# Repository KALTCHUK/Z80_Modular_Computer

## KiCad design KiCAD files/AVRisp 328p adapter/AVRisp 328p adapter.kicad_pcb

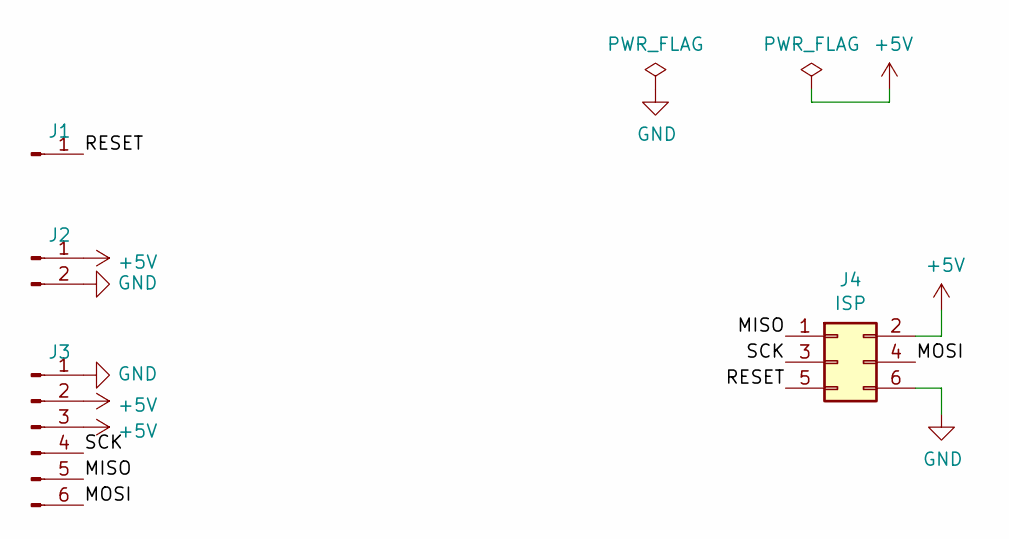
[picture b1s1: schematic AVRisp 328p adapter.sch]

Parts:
J1: Conn_01x01_Male; PinHeader_1x01_P2.54mm_Vertical
J2: Conn_01x02_Male; PinHeader_1x02_P2.54mm_Vertical
J3: Conn_01x06_Male; PinHeader_1x06_P2.54mm_Vertical
J4: ISP; PinHeader_2x03_P2.54mm_Vertical

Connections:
+5V: J2.1, J3.2, J3.3, J4.2
/MISO: J3.5, J4.1
/MOSI: J3.6, J4.4
/RESET: J1.1, J4.5
/SCK: J3.4, J4.3
GND: J2.2, J3.1, J4.6

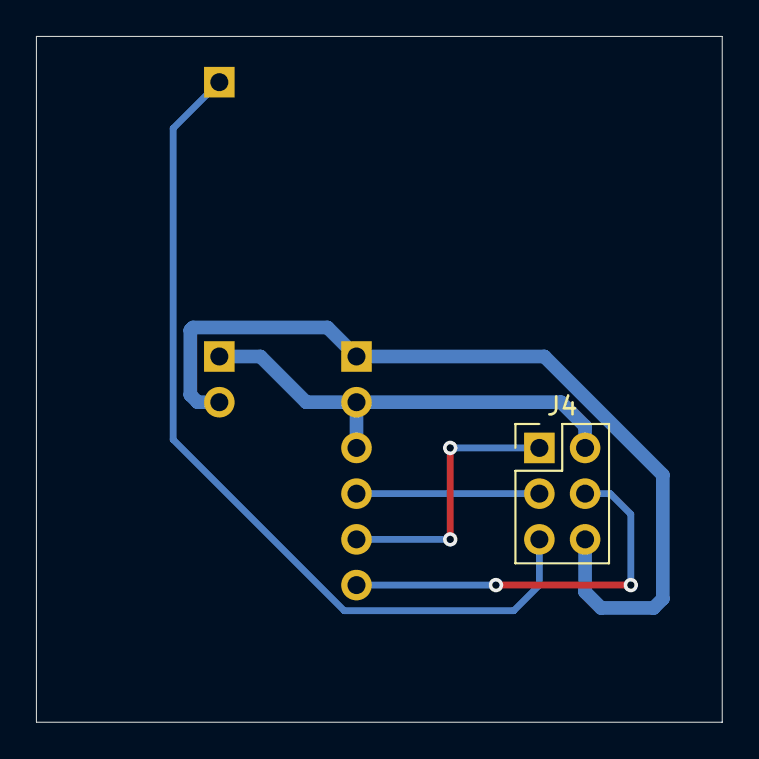
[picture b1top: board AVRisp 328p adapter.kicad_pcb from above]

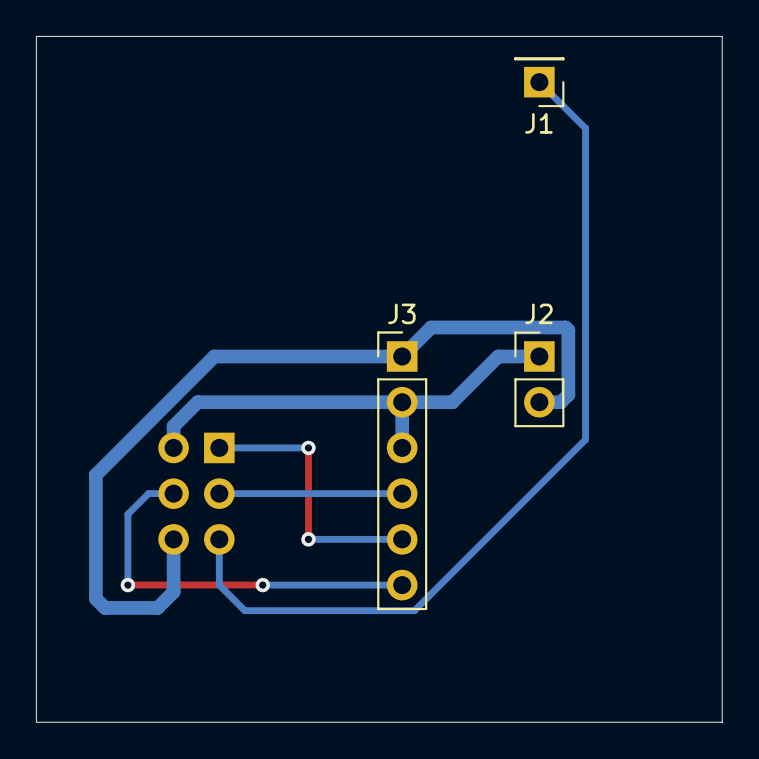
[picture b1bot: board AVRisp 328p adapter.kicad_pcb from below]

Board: 2 copper layers, 38.1 x 38.1 mm, 4 parts (3 on the bottom side), 6 nets.

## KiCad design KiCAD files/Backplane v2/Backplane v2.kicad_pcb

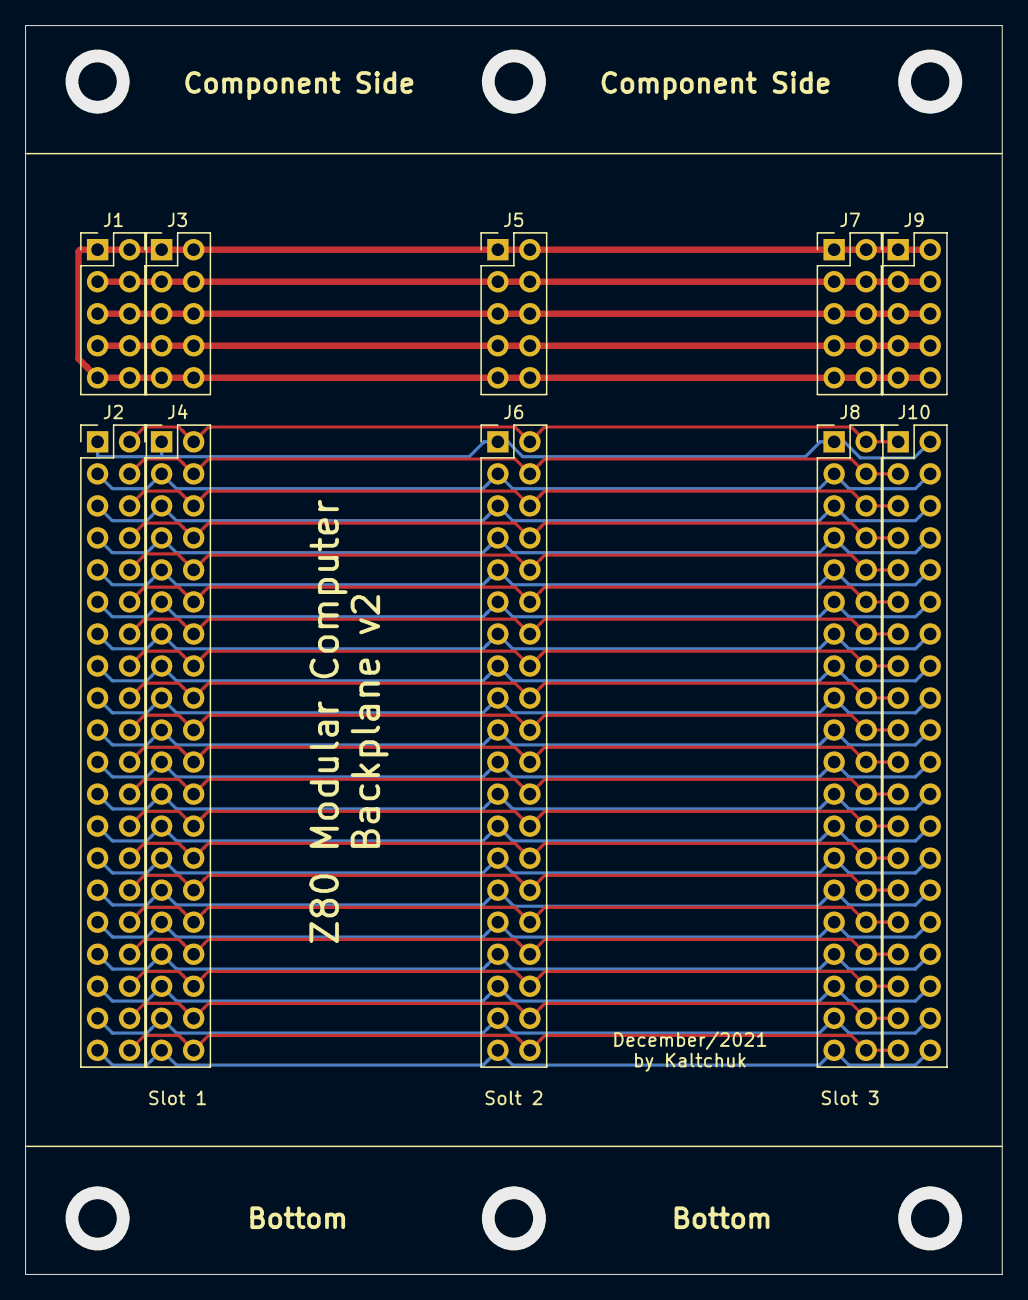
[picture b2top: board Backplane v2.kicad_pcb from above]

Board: 2 copper layers, 77.5 x 99.1 mm, 10 parts (0 on the bottom side), 44 nets.

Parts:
J1, J3, J5, J7, J9: Conn_02x05_Odd_Even; PinHeader_2x05_P2.54mm_Vertical
J2, J4, J6, J8, J10: Conn_02x20_Odd_Even; PinHeader_2x20_P2.54mm_Vertical

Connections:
/+5V: J1.3, J1.4, J3.3, J3.4, J5.3, J5.4, J7.3, J7.4, J9.3, J9.4
/+12V: J1.5, J1.6, J3.5, J3.6, J5.5, J5.6, J7.5, J7.6, J9.5, J9.6
/a00: J2.1, J4.1, J6.1, J8.1, J10.2
/a01: J2.2, J4.2, J6.2, J8.2, J10.1
/a02: J2.3, J4.3, J6.3, J8.3, J10.4
/a03: J2.4, J4.4, J6.4, J8.4, J10.3
/a04: J2.5, J4.5, J6.5, J8.5, J10.6
/a05: J2.6, J4.6, J6.6, J8.6, J10.5
/a06: J2.7, J4.7, J6.7, J8.7, J10.8
/a07: J2.8, J4.8, J6.8, J8.8, J10.7
/a08: J2.9, J4.9, J6.9, J8.9, J10.10
/a09: J2.10, J4.10, J6.10, J8.10, J10.9
/a10: J2.11, J4.11, J6.11, J8.11, J10.12
/a11: J2.12, J4.12, J6.12, J8.12, J10.11
/a12: J2.13, J4.13, J6.13, J8.13, J10.14
/a13: J2.14, J4.14, J6.14, J8.14, J10.13
/a14: J2.15, J4.15, J6.15, J8.15, J10.16
/a15: J2.16, J4.16, J6.16, J8.16, J10.15
/busack: J2.30, J4.30, J6.30, J8.30, J10.29
/busrq: J2.29, J4.29, J6.29, J8.29, J10.30
/clk: J2.40, J4.40, J6.40, J8.40, J10.39
/d00: J2.17, J4.17, J6.17, J8.17, J10.18
/d01: J2.18, J4.18, J6.18, J8.18, J10.17
/d02: J2.19, J4.19, J6.19, J8.19, J10.20
/d03: J2.20, J4.20, J6.20, J8.20, J10.19
/d04: J2.21, J4.21, J6.21, J8.21, J10.22
/d05: J2.22, J4.22, J6.22, J8.22, J10.21
/d06: J2.23, J4.23, J6.23, J8.23, J10.24
/d07: J2.24, J4.24, J6.24, J8.24, J10.23
/gnd: J1.1, J1.2, J1.9, J1.10, J3.1, J3.2, J3.9, J3.10, J5.1, J5.2, J5.9, J5.10, J7.1, J7.2, J7.9, J7.10, J9.1, J9.2, J9.9, J9.10
/halt: J2.32, J4.32, J6.32, J8.32, J10.31
/int: J2.34, J4.34, J6.34, J8.34, J10.33
/iorq: J2.27, J4.27, J6.27, J8.27, J10.28
/m1: J2.38, J4.38, J6.38, J8.38, J10.37
/mreq: J2.25, J4.25, J6.25, J8.25, J10.26
/nmi: J2.33, J4.33, J6.33, J8.33, J10.34
/rd: J2.28, J4.28, J6.28, J8.28, J10.27
/reset: J2.39, J4.39, J6.39, J8.39, J10.40
/s0: J2.35, J4.35, J6.35, J8.35, J10.36
/s1: J2.36, J4.36, J6.36, J8.36, J10.35
/s2: J2.37, J4.37, J6.37, J8.37, J10.38
/v1: J1.7, J1.8, J3.7, J3.8, J5.7, J5.8, J7.7, J7.8, J9.7, J9.8
/wait: J2.31, J4.31, J6.31, J8.31, J10.32
/wr: J2.26, J4.26, J6.26, J8.26, J10.25

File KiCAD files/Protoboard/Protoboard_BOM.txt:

J1	Power Bus	Connector_PinHeader_2.54mm:PinHeader_2x05_P2.54mm_Vertical	~	1
    J2	Signal Bus	Connector_PinHeader_2.54mm:PinHeader_2x20_P2.54mm_Vertical	~	1
    J3	Power	Connector_PinHeader_2.54mm:PinHeader_1x04_P2.54mm_Vertical	~	1
    J4	ADDR LO	Connector_PinHeader_2.54mm:PinHeader_1x08_P2.54mm_Vertical	~	1
    J5	ADDR HI	Connector_PinHeader_2.54mm:PinHeader_1x08_P2.54mm_Vertical	~	1
    J6	DATA	Connector_PinHeader_2.54mm:PinHeader_1x08_P2.54mm_Vertical	~	1
    J7	BUS CTRL	Connector_PinHeader_2.54mm:PinHeader_1x06_P2.54mm_Vertical	~	1
    J8	TIME CTRL	Connector_PinHeader_2.54mm:PinHeader_1x04_P2.54mm_Vertical	~	1
    J9	AUX SIGNAL	Connector_PinHeader_2.54mm:PinHeader_1x06_P2.54mm_Vertical	~	1

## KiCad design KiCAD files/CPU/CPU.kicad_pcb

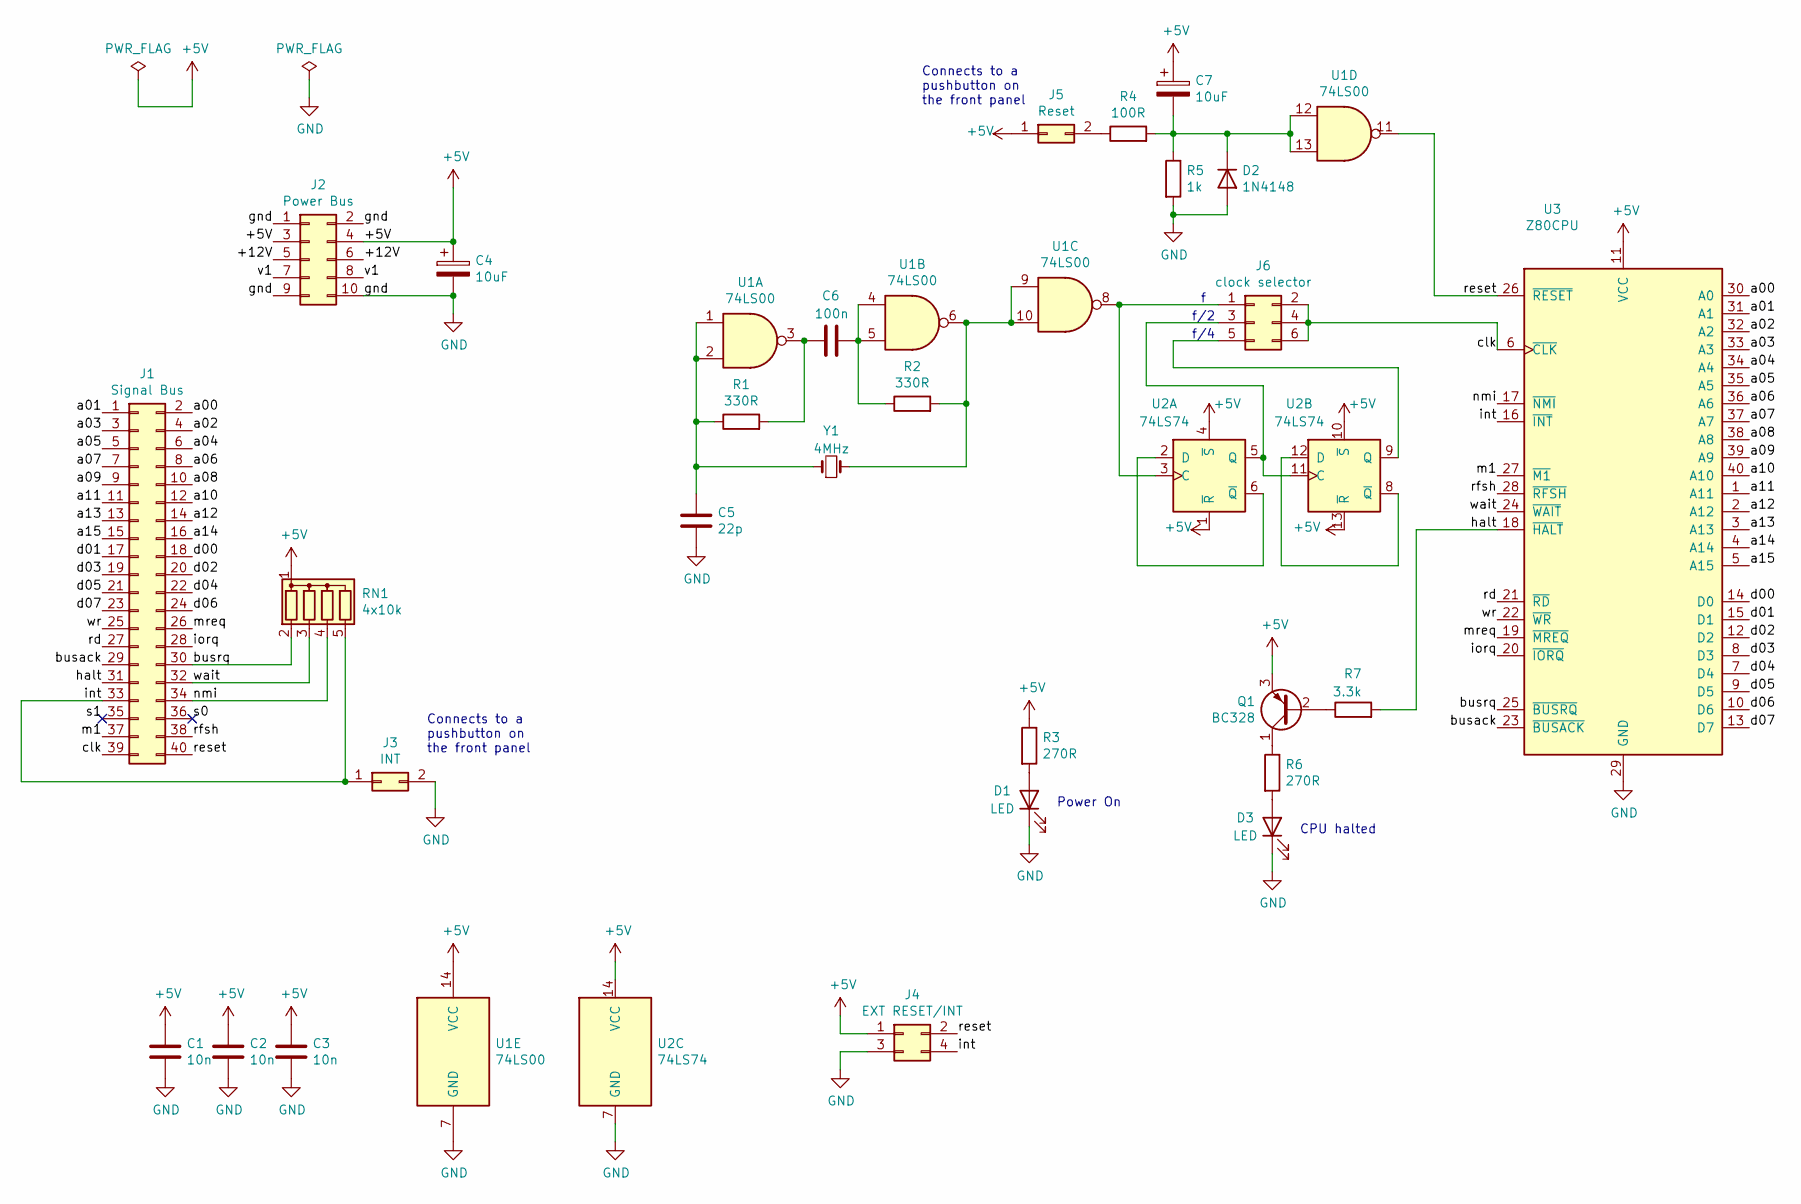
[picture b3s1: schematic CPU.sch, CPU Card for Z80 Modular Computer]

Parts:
C1, C2, C3: 10n; C_Disc_D3.8mm_W2.6mm_P2.50mm
C4, C7: 10uF; CP_Radial_D5.0mm_P2.50mm
C5: 22p; C_Disc_D3.8mm_W2.6mm_P2.50mm
C6: 100n; C_Disc_D3.8mm_W2.6mm_P2.50mm
D1, D3: LED; LED_D3.0mm
D2: 1N4148; D_DO-35_SOD27_P7.62mm_Horizontal
J1: Signal Bus; PinHeader_2x20_P2.54mm_Vertical
J2: Power Bus; PinHeader_2x05_P2.54mm_Vertical
J3: INT; PinHeader_2x01_P2.54mm_Vertical
J4: EXT RESET/INT; PinHeader_2x02_P2.54mm_Vertical
J5: Reset; PinHeader_2x01_P2.54mm_Vertical
J6: clock selector; PinHeader_2x03_P2.54mm_Vertical
Q1: BC328; TO-92_Inline
R1, R2: 330R; R_Axial_DIN0207_L6.3mm_D2.5mm_P10.16mm_Horizontal
R3, R6: 270R; R_Axial_DIN0207_L6.3mm_D2.5mm_P10.16mm_Horizontal
R4: 100R; R_Axial_DIN0207_L6.3mm_D2.5mm_P10.16mm_Horizontal
R5: 1k; R_Axial_DIN0207_L6.3mm_D2.5mm_P10.16mm_Horizontal
R7: 3.3k; R_Axial_DIN0207_L6.3mm_D2.5mm_P10.16mm_Horizontal
RN1: 4x10k; R_Array_SIP5
U1: 74LS00; DIP-14_W7.62mm_Socket_LongPads
U2: 74LS74; DIP-14_W7.62mm_Socket_LongPads
U3: Z80CPU; DIP-40_W25.4mm_Socket_LongPads
Y1: 4MHz; Crystal_HC49-U_Vertical

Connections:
+5V: C1.1, C2.1, C3.1, C4.1, C7.1, J2.3, J2.4, J4.1, J5.1, Q1.3 (E), R3.1, RN1.1 (common), U1.14 (VCC), U2.1 (~R), U2.4 (~S), U2.10 (~S), U2.13 (~R), U2.14 (VCC), U3.11 (VCC)
/+12V: J2.5, J2.6
/a00: J1.2, U3.30 (A0)
/a01: J1.1, U3.31 (A1)
/a02: J1.4, U3.32 (A2)
/a03: J1.3, U3.33 (A3)
/a04: J1.6, U3.34 (A4)
/a05: J1.5, U3.35 (A5)
/a06: J1.8, U3.36 (A6)
/a07: J1.7, U3.37 (A7)
/a08: J1.10, U3.38 (A8)
/a09: J1.9, U3.39 (A9)
/a10: J1.12, U3.40 (A10)
/a11: J1.11, U3.1 (A11)
/a12: J1.14, U3.2 (A12)
/a13: J1.13, U3.3 (A13)
/a14: J1.16, U3.4 (A14)
/a15: J1.15, U3.5 (A15)
/busack: J1.29, U3.23 (~BUSACK~)
/busrq: J1.30, RN1.2 (R1), U3.25 (~BUSRQ~)
/clk: J1.39, J6.2, J6.4, J6.6, U3.6 (~CLK~)
/d00: J1.18, U3.14 (D0)
/d01: J1.17, U3.15 (D1)
/d02: J1.20, U3.12 (D2)
/d03: J1.19, U3.8 (D3)
/d04: J1.22, U3.7 (D4)
/d05: J1.21, U3.9 (D5)
/d06: J1.24, U3.10 (D6)
/d07: J1.23, U3.13 (D7)
/halt: J1.31, R7.2, U3.18 (~HALT~)
/int: J1.33, J3.1, J4.4, RN1.5 (R4), U3.16 (~INT~)
/iorq: J1.28, U3.20 (~IORQ~)
/m1: J1.37, U3.27 (~M1~)
/mreq: J1.26, U3.19 (~MREQ~)
/nmi: J1.34, RN1.4 (R3), U3.17 (~NMI~)
/rd: J1.27, U3.21 (~RD~)
/reset: J1.40, J4.2, U1.11, U3.26 (~RESET~)
/rfsh: J1.38, U3.28 (~RFSH~)
/s0: J1.36
/s1: J1.35
/v1: J2.7, J2.8
/wait: J1.32, RN1.3 (R2), U3.24 (~WAIT~)
/wr: J1.25, U3.22 (~WR~)
GND: C1.2, C2.2, C3.2, C4.2, C5.2, D1.1 (K), D2.2 (A), D3.1 (K), J2.1, J2.2, J2.9, J2.10, J3.2, J4.3, R5.2, U1.7 (GND), U2.7 (GND), U3.29 (GND)
unnamed: C5.1, R1.1, U1.1, U1.2, Y1.1
unnamed: C6.1, R1.2, U1.3
unnamed: C6.2, R2.1, U1.4, U1.5
unnamed: C7.2, D2.1 (K), R4.2, R5.1, U1.12, U1.13
unnamed: D1.2 (A), R3.2
unnamed: D3.2 (A), R6.2
unnamed: J5.2, R4.1
unnamed: J6.1, U1.8, U2.3 (C)
unnamed: J6.3, U2.5 (Q), U2.11 (C)
unnamed: J6.5, U2.9 (Q)
unnamed: Q1.1 (C), R6.1
unnamed: Q1.2 (B), R7.1
unnamed: R2.2, U1.6, U1.9, U1.10, Y1.2
unnamed: U2.2 (D), U2.6 (~Q)
unnamed: U2.8 (~Q), U2.12 (D)

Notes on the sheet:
f/2
f/4
CPU halted
Power On
Connects to a pushbutton on the front panel

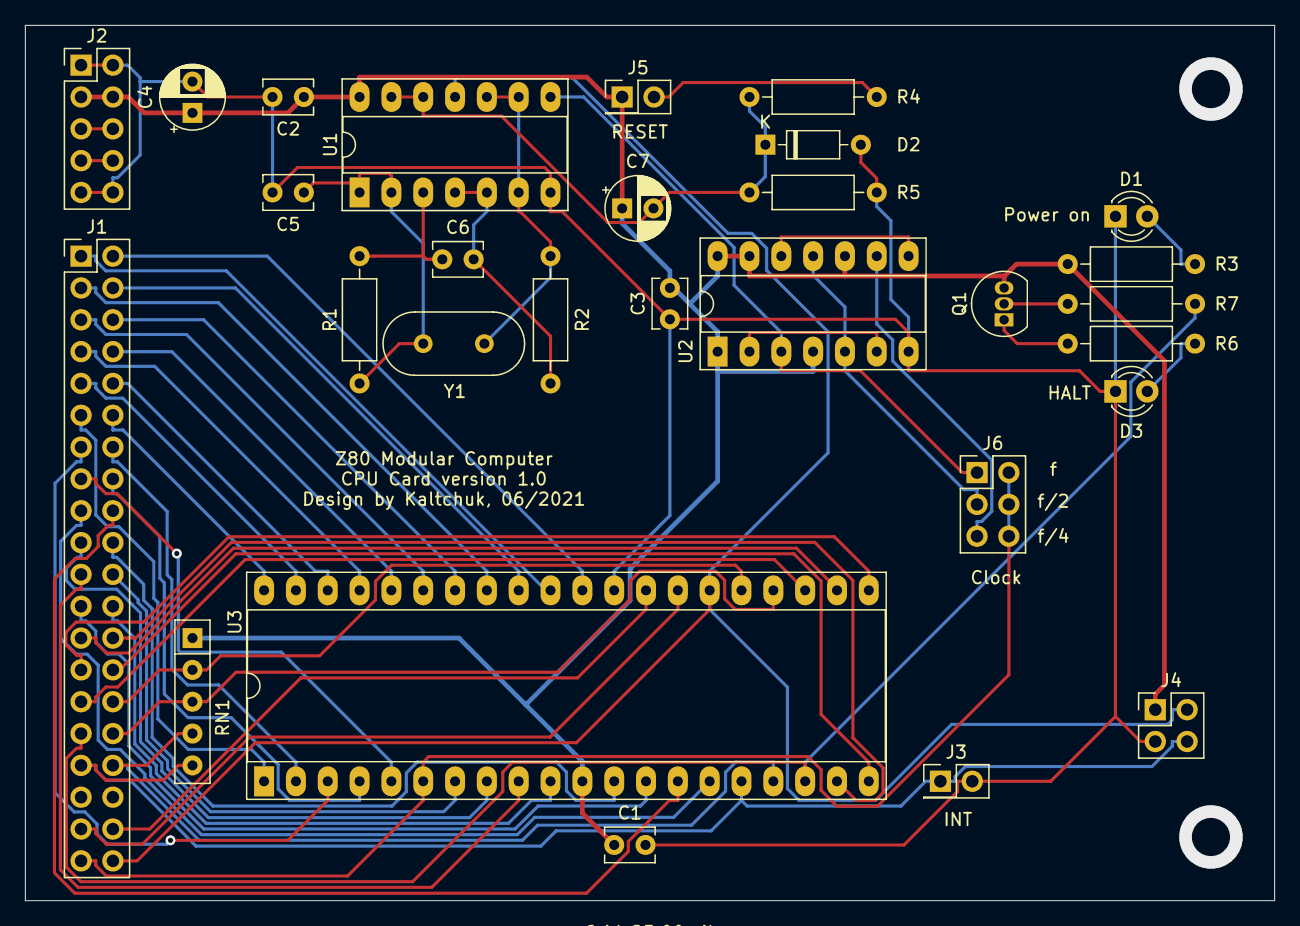
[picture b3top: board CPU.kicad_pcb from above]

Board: 2 copper layers, 99.7 x 69.8 mm, 29 parts (0 on the bottom side), 57 nets.

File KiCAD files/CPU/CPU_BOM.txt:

REFERENCE	QTY	VALUE		DESCRIPTION							
-----------------------------------------------------------------------------------------------------------
  C1-C3		3	10n		Capacitor_THT:C_Disc_D3.8mm_W2.6mm_P2.50mm			
  C4, C7	1	10uF		Capacitor_THT:CP_Radial_D5.0mm_P2.50mm				
    C5		1	22p		Capacitor_THT:C_Disc_D3.8mm_W2.6mm_P2.50mm			
    C6		1	100n		Capacitor_THT:C_Disc_D3.8mm_W2.6mm_P2.50mm			
    D2		1	1N4148		Diode_THT:D_DO-35_SOD27_P7.62mm_Horizontal	 		
  D1, D3	2	LED		LED_THT:LED_D3.0mm (1 x green, 1 x yellow)			
    J1		1	Signal Bus	Connector_PinHeader_2.54mm:PinHeader_2x20_P2.54mm_90_deg_female	
    J2		1	Power Bus	Connector_PinHeader_2.54mm:PinHeader_2x05_P2.54mm_90_deg_female	
    J5		1	Reset		Push button 1 pole 3mm hole							
    J6		1	clock selector	Connector_PinHeader_2.54mm:PinHeader_2x03_P2.54mm_Vertical	
    Q1		1	BC328		Package_TO_SOT_THT:TO-92_Inline					
  R1, R2	2	330R		Resistor_THT:R_Axial_DIN0207_L6.3mm_D2.5mm_P10.16mm
    R4		1	100R		Resistor_THT:R_Axial_DIN0207_L6.3mm_D2.5mm_P10.16mm
    R5		1	1k		Resistor_THT:R_Axial_DIN0207_L6.3mm_D2.5mm_P10.16mm
  R3, R6	2	270R		Resistor_THT:R_Axial_DIN0207_L6.3mm_D2.5mm_P10.16mm
    R7		2	3.3k		Resistor_THT:R_Axial_DIN0207_L6.3mm_D2.5mm_P10.16mm
    RN1		1	4x10k		Resistor_THT:R_Array_SIP5
    U1		1	74LS00		Package_DIP:DIP-14_W7.62mm_Socket_LongPads
    U2		1	74LS74		Package_DIP:DIP-14_W7.62mm_Socket_LongPads
    U3		1	Z80CPU		Package_DIP:DIP-40_W25.4mm_Socket_LongPads
    Y1		1	10MHz		Crystal:Crystal_HC49-U_Vertical					
		1	PCB		CPU PCB
		1	Fontal		CPU frontal

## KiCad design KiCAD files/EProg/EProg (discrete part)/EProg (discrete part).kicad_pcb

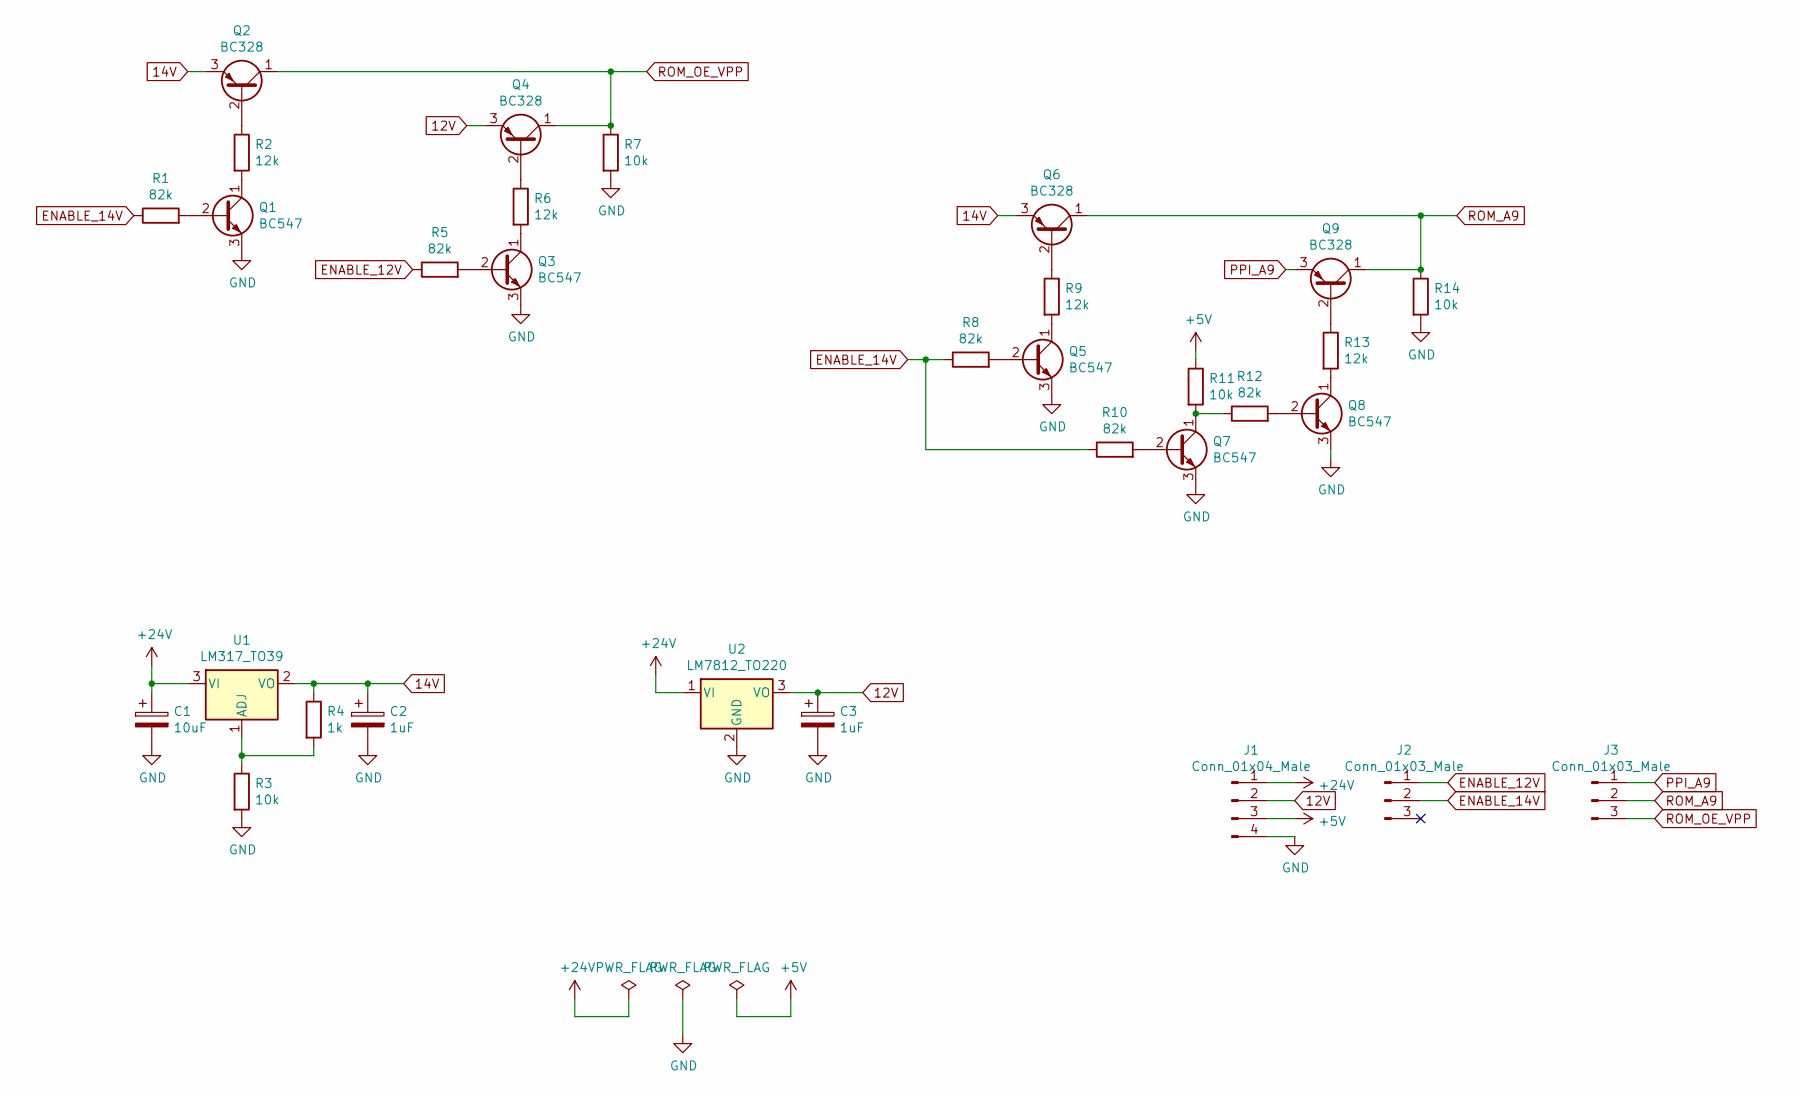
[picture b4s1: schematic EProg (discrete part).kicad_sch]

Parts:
C1: 10uF; CP_Radial_D5.0mm_P2.50mm
C2, C3: 1uF; CP_Radial_D5.0mm_P2.50mm
J1: Conn_01x04_Male; PinHeader_1x04_P2.54mm_Horizontal
J2, J3: Conn_01x03_Male; PinHeader_1x03_P2.54mm_Horizontal
Q1, Q3, Q5, Q7, Q8: BC547; TO-92_Inline
Q2, Q4, Q6, Q9: BC328; TO-92_Inline
R1, R5, R8, R10, R12: 82k; R_Axial_DIN0207_L6.3mm_D2.5mm_P7.62mm_Horizontal
R2, R6, R9, R13: 12k; R_Axial_DIN0207_L6.3mm_D2.5mm_P7.62mm_Horizontal
R3, R7, R11, R14: 10k; R_Axial_DIN0207_L6.3mm_D2.5mm_P7.62mm_Horizontal
R4: 1k; R_Axial_DIN0207_L6.3mm_D2.5mm_P7.62mm_Horizontal
U1: LM317_TO39; TO-39-3
U2: LM7812_TO220; TO-220-3_Vertical

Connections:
12V: C3.1, J1.2, Q4.3 (E), U2.3 (VO)
14V: C2.1, Q2.3 (E), Q6.3 (E), R4.1, U1.2 (VO)
+5V: J1.3, R11.1
+24V: C1.1, J1.1, U1.3 (VI), U2.1 (VI)
ENABLE_12V: J2.1, R5.1
ENABLE_14V: J2.2, R1.1, R8.1, R10.1
GND: C1.2, C2.2, C3.2, J1.4, Q1.3 (E), Q3.3 (E), Q5.3 (E), Q7.3 (E), Q8.3 (E), R3.2, R7.2, R14.2, U2.2 (GND)
unnamed: Q1.1 (C), R2.2
unnamed: Q1.2 (B), R1.2
unnamed: Q2.2 (B), R2.1
unnamed: Q3.1 (C), R6.2
unnamed: Q3.2 (B), R5.2
unnamed: Q4.2 (B), R6.1
unnamed: Q5.1 (C), R9.2
unnamed: Q5.2 (B), R8.2
unnamed: Q6.2 (B), R9.1
unnamed: Q7.1 (C), R11.2, R12.1
unnamed: Q7.2 (B), R10.2
unnamed: Q8.1 (C), R13.2
unnamed: Q8.2 (B), R12.2
unnamed: Q9.2 (B), R13.1
unnamed: R3.1, R4.2, U1.1 (ADJ)
PPI_A9: J3.1, Q9.3 (E)
ROM_A9: J3.2, Q6.1 (C), Q9.1 (C), R14.1
ROM_OE_VPP: J3.3, Q2.1 (C), Q4.1 (C), R7.1

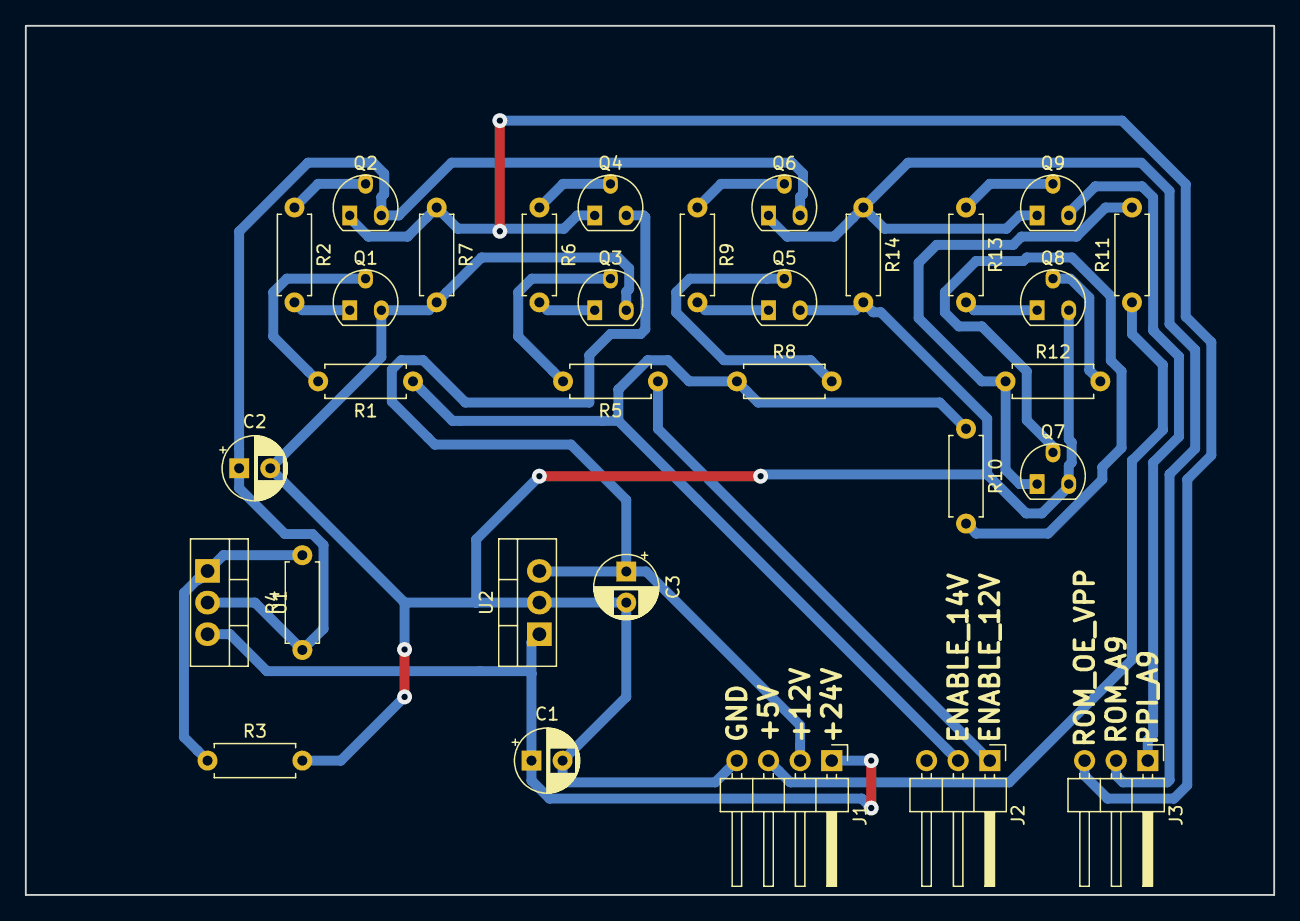
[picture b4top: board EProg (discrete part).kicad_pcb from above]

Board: 2 copper layers, 100.3 x 69.8 mm, 31 parts (0 on the bottom side), 25 nets.

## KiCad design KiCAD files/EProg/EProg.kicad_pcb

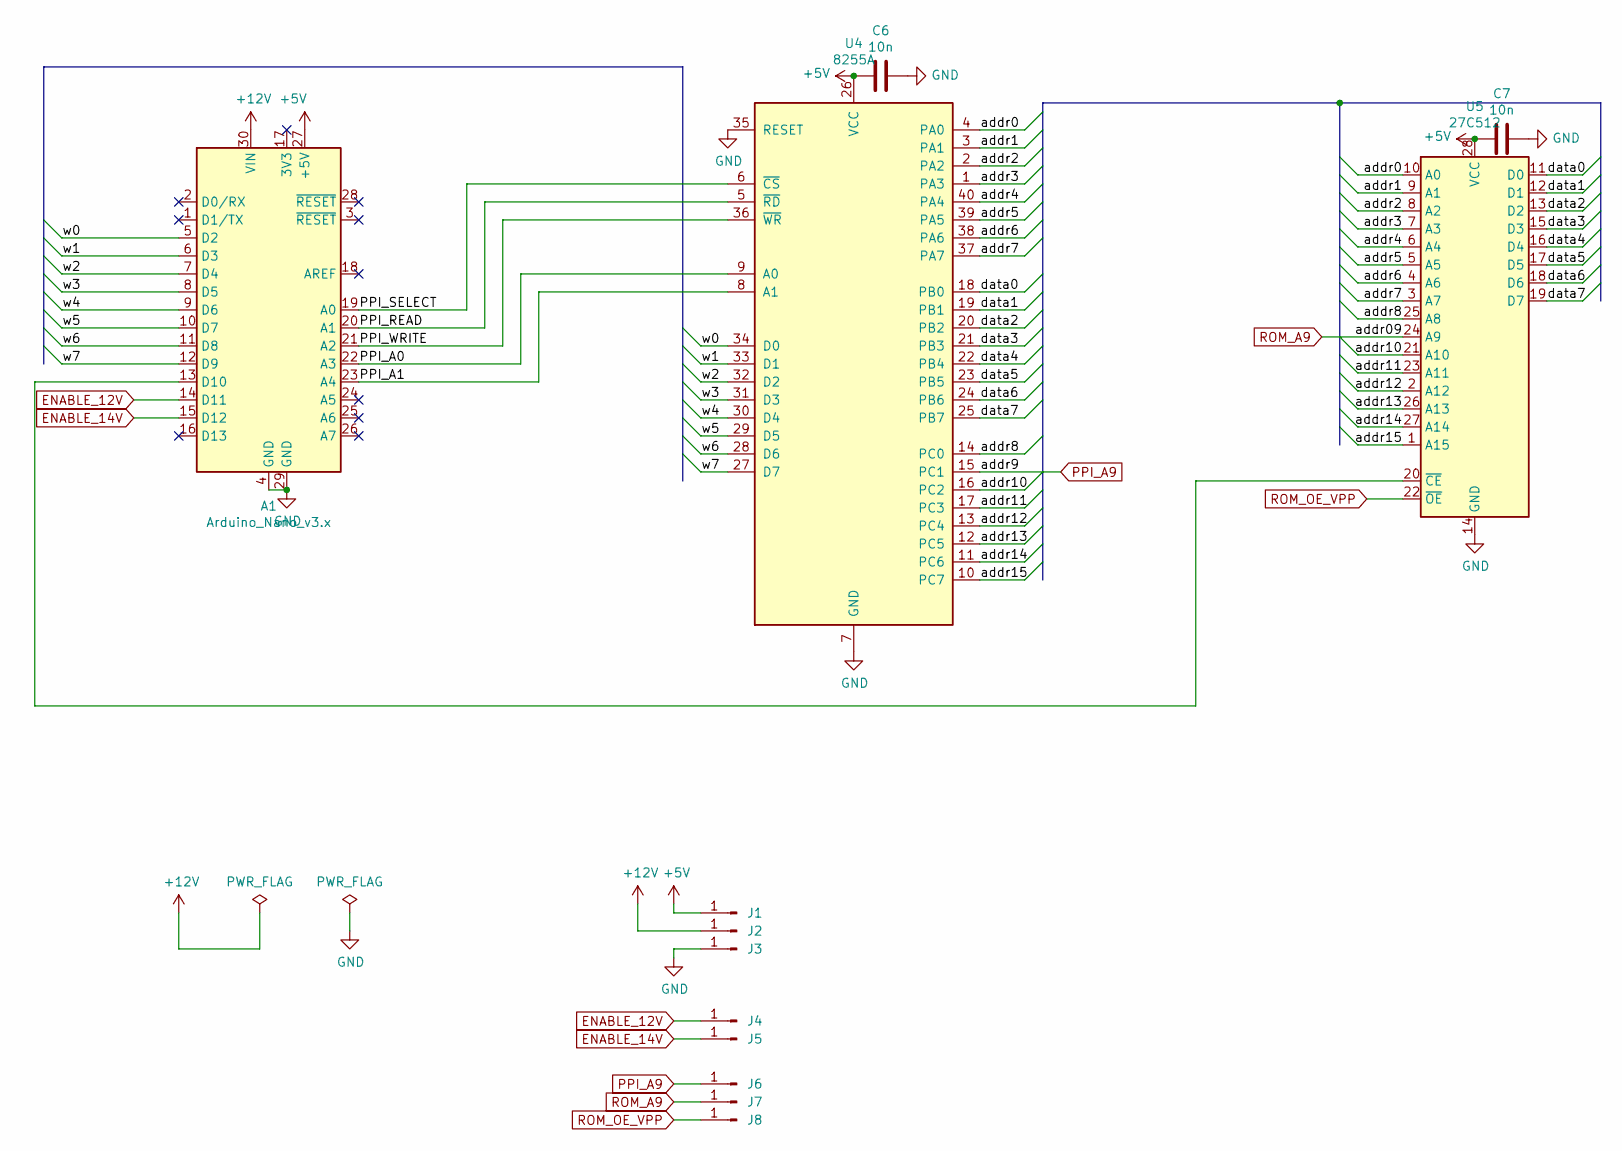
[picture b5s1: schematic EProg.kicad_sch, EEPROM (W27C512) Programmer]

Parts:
A1: Arduino_Nano_v3.x; Arduino_Nano
C6, C7: 10n; C_Disc_D3.0mm_W2.0mm_P2.50mm
J1, J2, J3, J4, J5, J6, J7, J8: Conn_01x01_Male; PinHeader_1x01_P2.54mm_Vertical
U4: 8255A; DIP-40_W15.24mm
U5: 27C512; DIP-28_W15.24mm

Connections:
+5V: A1.27 (+5V), C6.1, C7.1, J1.1, U4.26 (VCC), U5.28 (VCC)
+12V: A1.30 (VIN), J2.1
/PPI_A0: A1.22 (A3), U4.9 (A0)
/PPI_A1: A1.23 (A4), U4.8 (A1)
/PPI_READ: A1.20 (A1), U4.5 (~RD)
/PPI_SELECT: A1.19 (A0), U4.6 (~CS)
/PPI_WRITE: A1.21 (A2), U4.36 (~WR)
/addr0: U4.4 (PA0), U5.10 (A0)
/addr1: U4.3 (PA1), U5.9 (A1)
/addr2: U4.2 (PA2), U5.8 (A2)
/addr3: U4.1 (PA3), U5.7 (A3)
/addr4: U4.40 (PA4), U5.6 (A4)
/addr5: U4.39 (PA5), U5.5 (A5)
/addr6: U4.38 (PA6), U5.4 (A6)
/addr7: U4.37 (PA7), U5.3 (A7)
/addr8: U4.14 (PC0), U5.25 (A8)
/addr10: U4.16 (PC2), U5.21 (A10)
/addr11: U4.17 (PC3), U5.23 (A11)
/addr12: U4.13 (PC4), U5.2 (A12)
/addr13: U4.12 (PC5), U5.26 (A13)
/addr14: U4.11 (PC6), U5.27 (A14)
/addr15: U4.10 (PC7), U5.1 (A15)
/data0: U4.18 (PB0), U5.11 (D0)
/data1: U4.19 (PB1), U5.12 (D1)
/data2: U4.20 (PB2), U5.13 (D2)
/data3: U4.21 (PB3), U5.15 (D3)
/data4: U4.22 (PB4), U5.16 (D4)
/data5: U4.23 (PB5), U5.17 (D5)
/data6: U4.24 (PB6), U5.18 (D6)
/data7: U4.25 (PB7), U5.19 (D7)
/w0: A1.5 (D2), U4.34 (D0)
/w1: A1.6 (D3), U4.33 (D1)
/w2: A1.7 (D4), U4.32 (D2)
/w3: A1.8 (D5), U4.31 (D3)
/w4: A1.9 (D6), U4.30 (D4)
/w5: A1.10 (D7), U4.29 (D5)
/w6: A1.11 (D8), U4.28 (D6)
/w7: A1.12 (D9), U4.27 (D7)
ENABLE_12V: A1.14 (D11), J4.1
ENABLE_14V: A1.15 (D12), J5.1
GND: A1.4 (GND), A1.29 (GND), C6.2, C7.2, J3.1, U4.7 (GND), U4.35 (RESET), U5.14 (GND)
unnamed: A1.13 (D10), U5.20 (~CE)
PPI_A9: J6.1, U4.15 (PC1)
ROM_A9: J7.1, U5.24 (A9)
ROM_OE_VPP: J8.1, U5.22 (~OE)

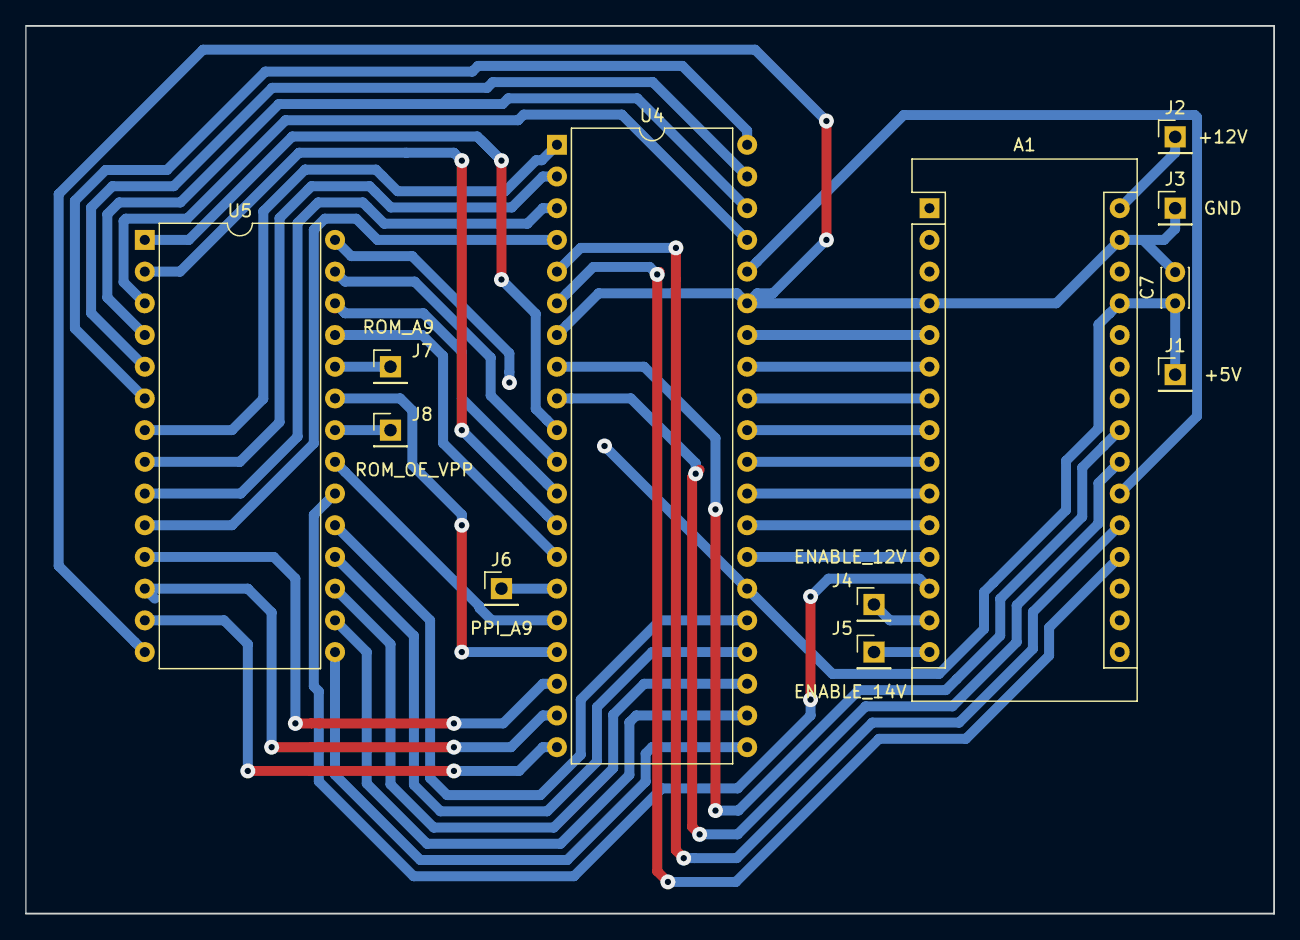
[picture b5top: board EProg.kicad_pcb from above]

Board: 2 copper layers, 100.0 x 71.1 mm, 12 parts (0 on the bottom side), 45 nets.
